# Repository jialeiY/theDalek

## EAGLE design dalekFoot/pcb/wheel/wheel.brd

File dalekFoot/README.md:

## For USART Only

## Control Request Packet
Offset | Name | Content | Width<br />(Bytes)
-:|:-|:-:|-:
0 | Packet Header | 0x55 | 1
1 | Motor Power # 1 | xx | 1
2 | Motor Power # 2 | xx | 1
3 | Motor Power # 3 | xx | 1
4 | Motor Power # 4 | xx | 1
5 | Melody Index | xx | 1
6 | LED | xx | 1
7 | CRC for payload only | xx | 1
8 | Packet Ending | 0xAA | 1

## Sampling Data Packet

Offset | Name | Content | Width<br />(Bytes)
-:|:-|:-:|-:
0 | Packet Header | 0x55 | 1
1 | Timestamp (Milliseconds) | xx | 4
5 | Time Offset (Micro Seconds) | xx | 4
9 | Motor Encoder #1 | xx | 2
11 | Motor Encoder #2 | xx | 2
13 | Motor Encoder #3 | xx | 2
15 | Motor Encoder #4 | xx | 2
17 | Fast ADC Value #1 ~ #14 | xx | 28
45 | Slow ADC Index | xx | 1
46 | Slow ADC Value | xx | 2
48 | UserInput | xx | 1
49 | CRC for payload only | xx  | 1
50 | Packet Ending | 0xAA | 1

# dalekFoot
## System Architecture

## MCU components connection diagram

## Neuro Software Architecture

## Protocol
### Working Scenario

### Startup Scenario

### Timeout Scenario

# stm32

## Interrupt NVIC

* Systick is the top piority timer

## Timer

* Systick is the top piority timer
* Systick should not block other event, It should be async and just make a notify

## SPI

* Max speed = 1/2 PCLK, SPI2 = 21MHz; SPI1 = 42MHz

## TODO

o DMA for SPI communication
o communication with SPI in slave mode
o communication with SPI and calculate the CPU usage

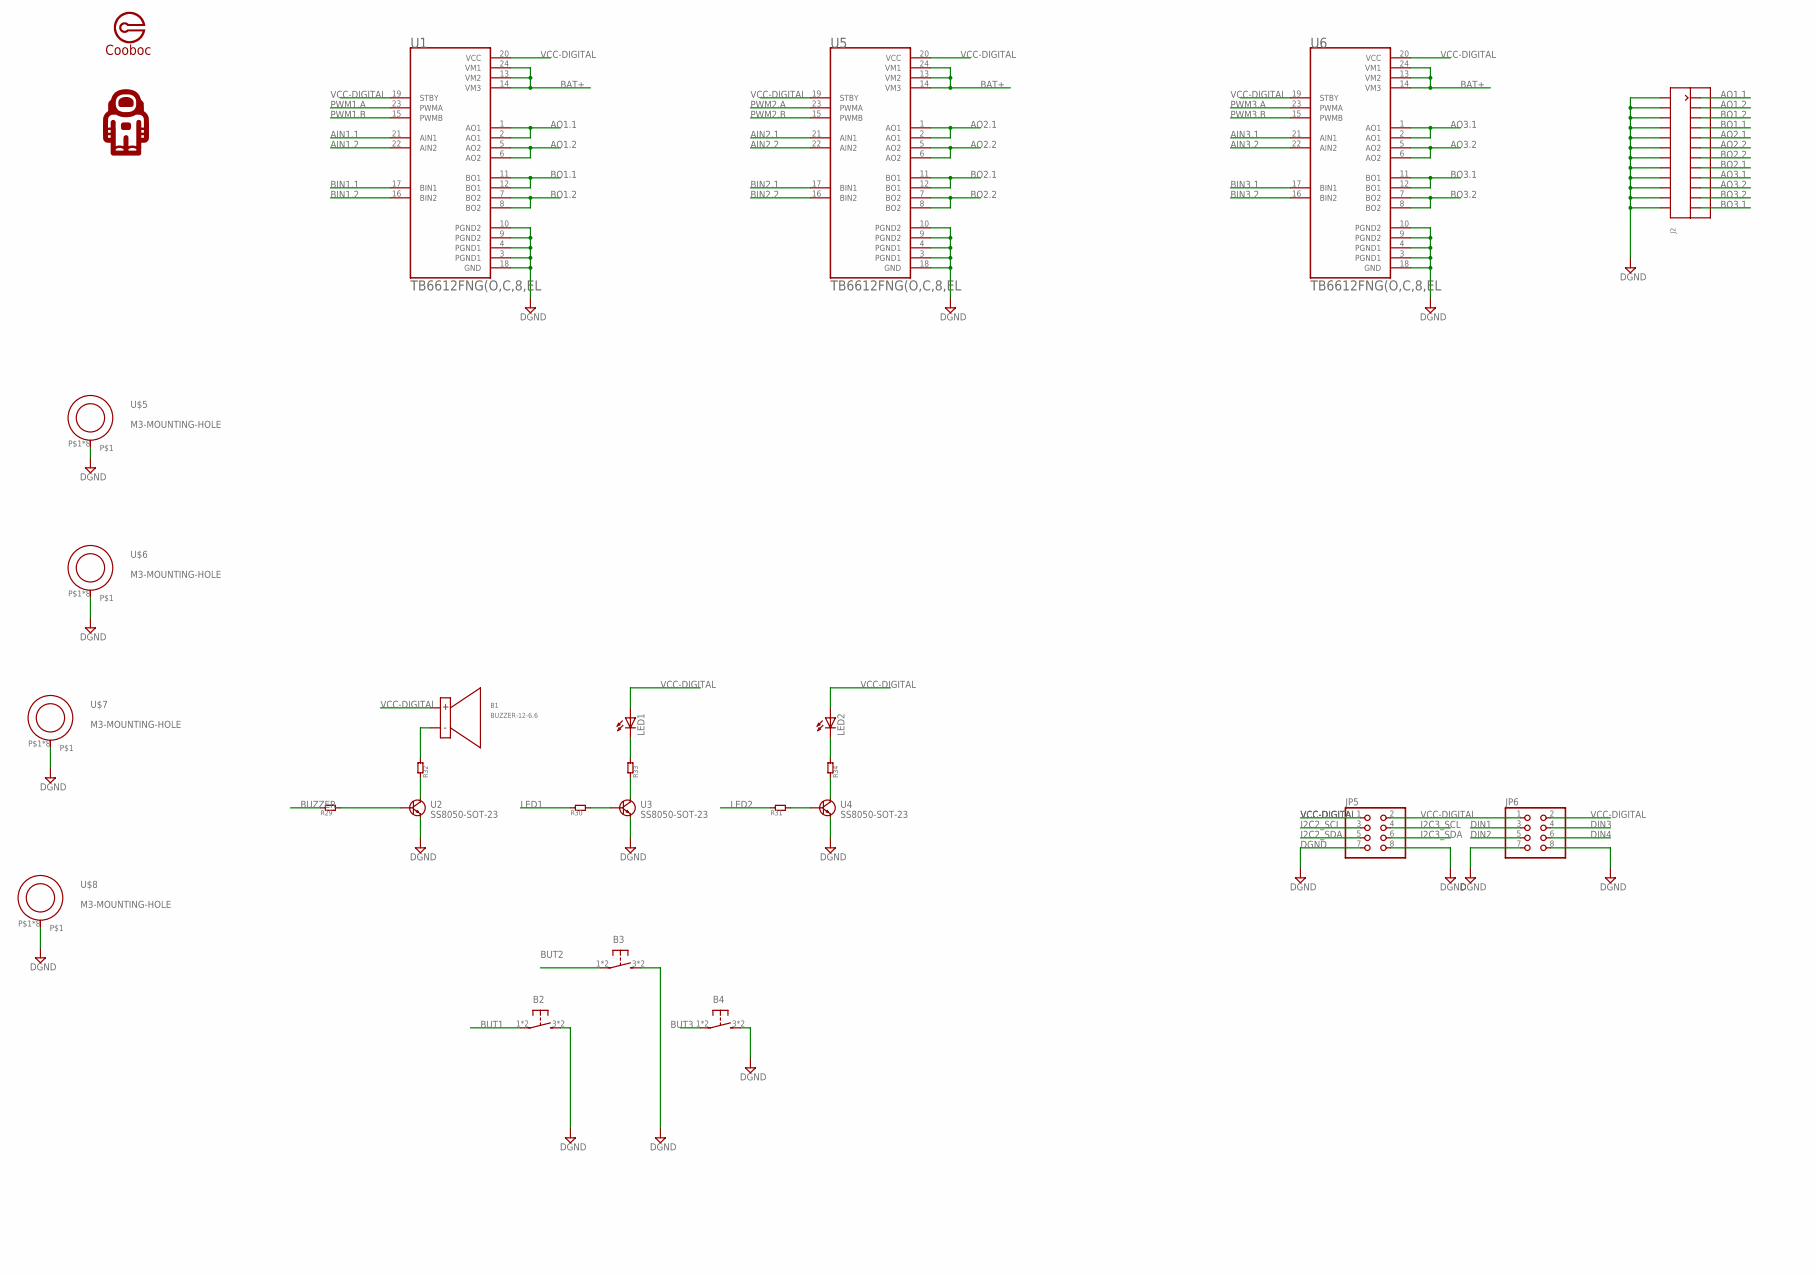
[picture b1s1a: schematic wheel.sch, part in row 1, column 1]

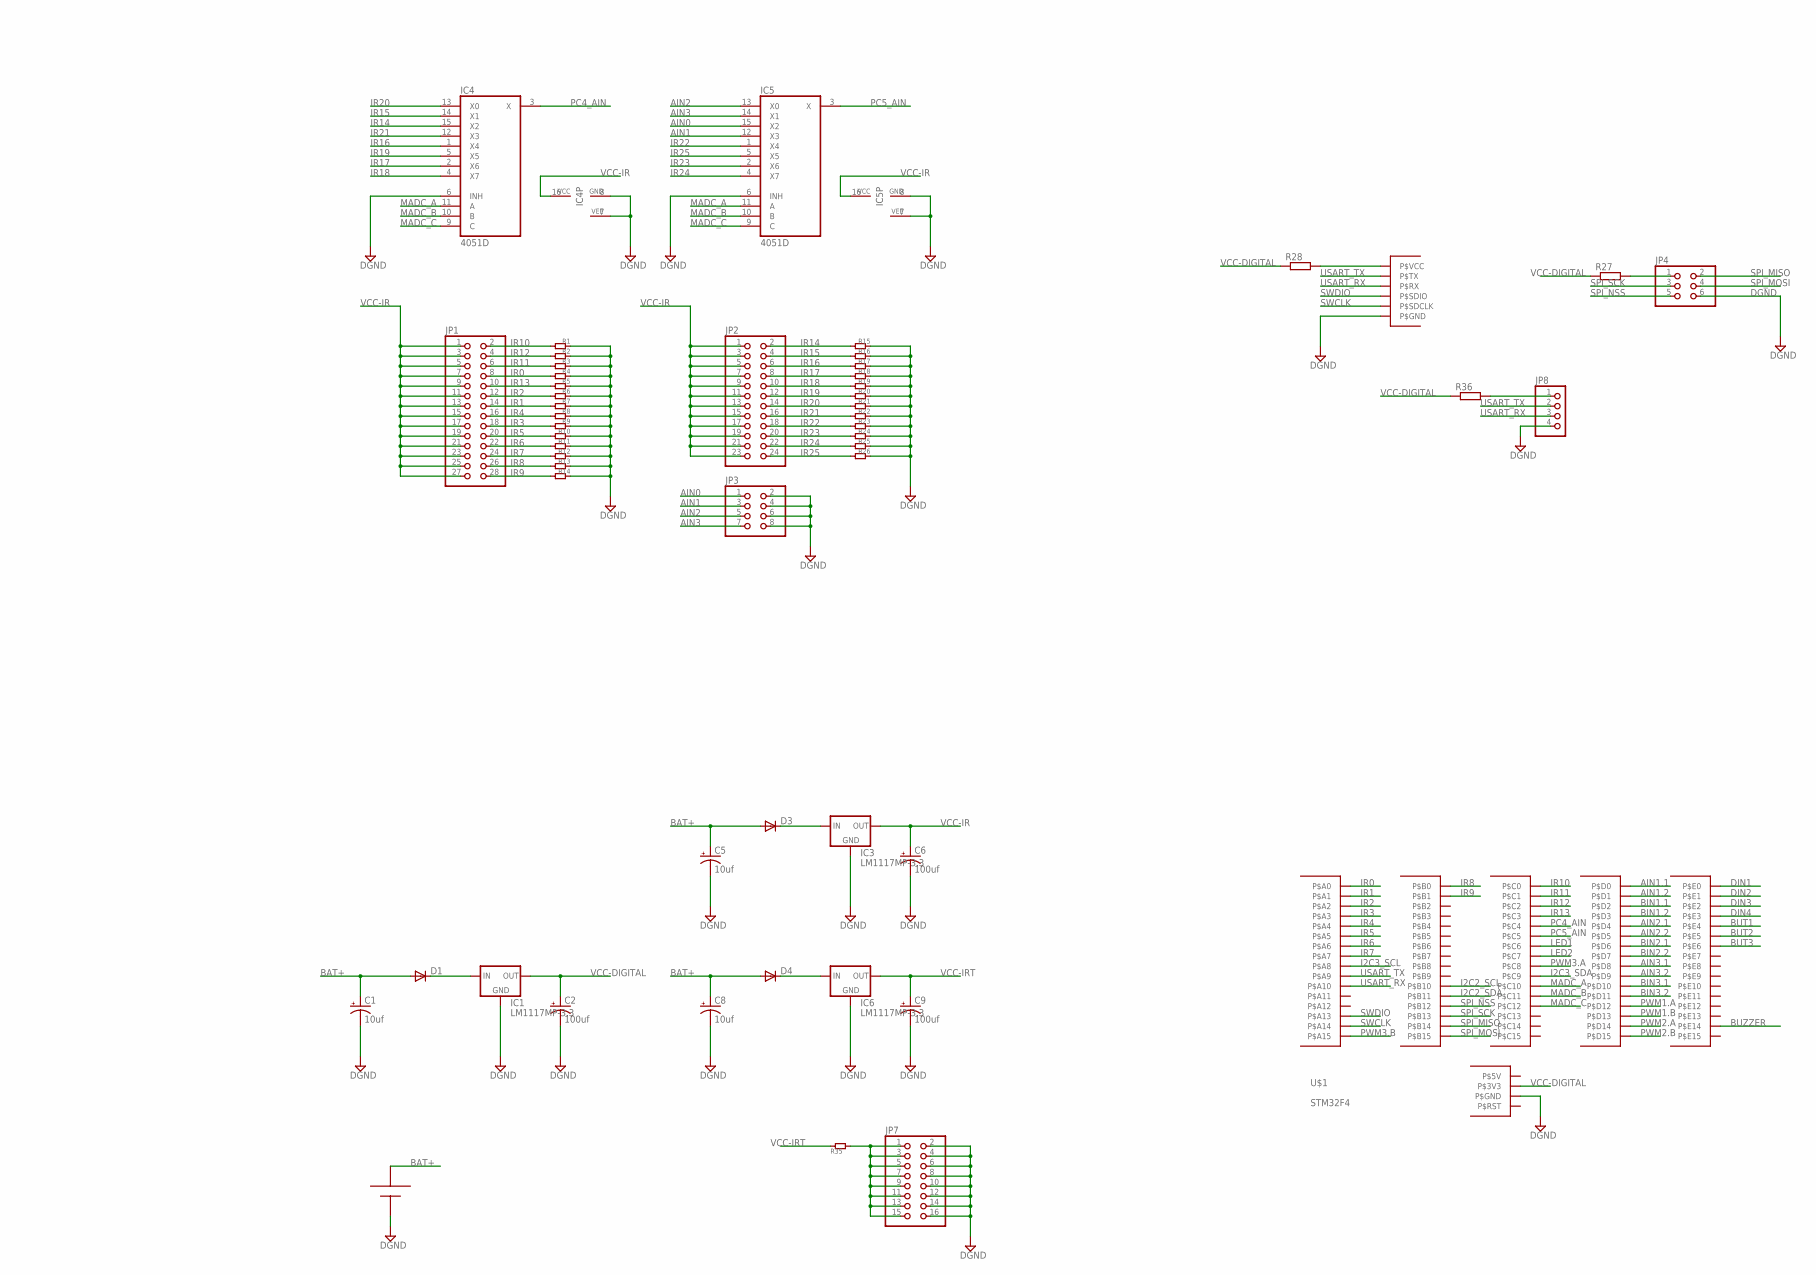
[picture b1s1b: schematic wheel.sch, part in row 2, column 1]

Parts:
B1: BUZZER-12-6.6
B2, B3, B4: DTSM-6-2PIN; DTSM-6
C1, C5, C8: 10uf; 153CLV-0505
C2, C6, C9: 100uf; 153CLV-0605
D1, D3, D4: DIODE-DO-214AC; DO-214AC
IC1, IC3, IC6: LM1117MP-3.3; SOT223
IC4, IC5: 4051D; SO16
J1: DEBUG-PORT
J2: KF250-2X12P
JP1: PINHD-2X14; 2X14
JP2: PINHD-2X12; 2X12
JP3, JP5, JP6: PINHD-2X4; 2X04
JP4: PINHD-2X3; 2X03
JP7: PINHD-2X8; 2X08
JP8: PINHD-1X4; 1X04
LED1, LED2: LEDCHIP-LED0805; CHIP-LED0805
R1, R2, R3, R4, R5, R6, R7, R8, R9, R10, R11, R12, R13, R14, R15, R16, R17, R18, R19, R20, R21, R22, R23, R24, R25, R26: R-0603; 0603
R27, R28, R36: R-EU_R0402; R0402
R29, R30, R31, R32, R33, R34, R35: R-0805; 0805
U1, U5, U6: TB6612FNG(O,C,8,EL; SOP65P760X160-24N
U2, U3, U4: SS8050-SOT-23; SOT-23
U$1: STM32F4
U$2: BATTERY-10A; BATTERY_10A
U$3: COOBOC-PLACE
U$4: ASTRONANT
U$5, U$6, U$7, U$8: M3-MOUNTING-HOLE

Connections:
AIN0: IC5.15 (X2), JP3.1
AIN1: IC5.12 (X3), JP3.3
AIN1.1: U1.21 (AIN1), U$1.P$22 (P$D0)
AIN1.2: U1.22 (AIN2), U$1.P$23 (P$D1)
AIN2: IC5.13 (X0), JP3.5
AIN2.1: U5.21 (AIN1), U$1.P$26 (P$D4)
AIN2.2: U5.22 (AIN2), U$1.P$27 (P$D5)
AIN3: IC5.14 (X1), JP3.7
AIN3.1: U6.21 (AIN1), U$1.P$49 (P$D8)
AIN3.2: U6.22 (AIN2), U$1.P$50 (P$D9)
AO1.1: J2.P$1, U1.1 (AO1), U1.2 (AO1)
AO1.2: J2.P$3, U1.5 (AO2), U1.6 (AO2)
AO2.1: J2.P$9, U5.1 (AO1), U5.2 (AO1)
AO2.2: J2.P$11, U5.5 (AO2), U5.6 (AO2)
AO3.1: J2.P$17, U6.1 (AO1), U6.2 (AO1)
AO3.2: J2.P$19, U6.5 (AO2), U6.6 (AO2)
BAT+: C1.+, C5.+, C8.+, D1.A, D3.A, D4.A, U1.13 (VM2), U1.14 (VM3), U1.24 (VM1), U5.13 (VM2), U5.14 (VM3), U5.24 (VM1), U6.13 (VM2), U6.14 (VM3), U6.24 (VM1), U$2.P$+ (P$POS)
BIN1.1: U1.17 (BIN1), U$1.P$24 (P$D2)
BIN1.2: U1.16 (BIN2), U$1.P$25 (P$D3)
BIN2.1: U5.17 (BIN1), U$1.P$28 (P$D6)
BIN2.2: U5.16 (BIN2), U$1.P$29 (P$D7)
BIN3.1: U6.17 (BIN1), U$1.P$51 (P$D10)
BIN3.2: U6.16 (BIN2), U$1.P$52 (P$D11)
BO1.1: J2.P$7, U1.11 (BO1), U1.12 (BO1)
BO1.2: J2.P$5, U1.7 (BO2), U1.8 (BO2)
BO2.1: J2.P$15, U5.11 (BO1), U5.12 (BO1)
BO2.2: J2.P$13, U5.7 (BO2), U5.8 (BO2)
BO3.1: J2.P$23, U6.11 (BO1), U6.12 (BO1)
BO3.2: J2.P$21, U6.7 (BO2), U6.8 (BO2)
BUT1: B2.1, B2.2 (1), U$1.P$61 (P$E4)
BUT2: B3.1, B3.2 (1), U$1.P$62 (P$E5)
BUT3: B4.1, B4.2 (1), U$1.P$63 (P$E6)
BUZZER: R29.P$1, U$1.P$41 (P$E14)
DGND: B2.3 (2), B2.4 (2), B3.3 (2), B3.4 (2), B4.3 (2), B4.4 (2), C1.-, C2.-, C5.-, C6.-, C8.-, C9.-, IC1.1 (GND), IC3.1 (GND), IC4.6 (INH), IC4.7 (VEE), IC4.8 (GND), IC5.6 (INH), IC5.7 (VEE), IC5.8 (GND), IC6.1 (GND), J1.P$7 (P$GND), J1.P$8 (P$GND), J2.P$2, J2.P$4, J2.P$6, J2.P$8, J2.P$10, J2.P$12, J2.P$14, J2.P$16, J2.P$18, J2.P$20, J2.P$22, J2.P$24, JP3.2, JP3.4, JP3.6, JP3.8, JP4.6, JP5.7, JP5.8, JP6.7, JP6.8, JP7.2, JP7.4, JP7.6, JP7.8, JP7.10, JP7.12, JP7.14, JP7.16, JP8.4, R1.P$1, R2.P$1, R3.P$1, R4.P$1, R5.P$1, R6.P$1, R7.P$1, R8.P$1, R9.P$1, R10.P$1, R11.P$1, R12.P$1, R13.P$1, R14.P$1, R15.P$1, R16.P$1, R17.P$1, R18.P$1, R19.P$1, R20.P$1, R21.P$1, R22.P$1, R23.P$1, R24.P$1, R25.P$1, R26.P$1, U1.3 (PGND1), U1.4 (PGND1), U1.9 (PGND2), U1.10 (PGND2), U1.18 (GND), U2.P$3 (P$E), U3.P$3 (P$E), U4.P$3 (P$E), U5.3 (PGND1), U5.4 (PGND1), U5.9 (PGND2), U5.10 (PGND2), U5.18 (GND), U6.3 (PGND1), U6.4 (PGND1), U6.9 (PGND2), U6.10 (PGND2), U6.18 (GND), U$1.P$1 (P$GND), U$1.P$2 (P$GND), U$1.P$3 (P$GND), U$1.P$91 (P$GND), U$1.P$92 (P$GND), U$2.P$- (P$NEG), U$5.P$1, U$5.P$2, U$5.P$3, U$5.P$4, U$5.P$5, U$5.P$6, U$5.P$7, U$5.P$8, U$6.P$1, U$6.P$2, U$6.P$3, U$6.P$4, U$6.P$5, U$6.P$6, U$6.P$7, U$6.P$8, U$7.P$1, U$7.P$2, U$7.P$3, U$7.P$4, U$7.P$5, U$7.P$6, U$7.P$7, U$7.P$8, U$8.P$1, U$8.P$2, U$8.P$3, U$8.P$4, U$8.P$5, U$8.P$6, U$8.P$7, U$8.P$8
DIN1: JP6.3, U$1.P$57 (P$E0)
DIN2: JP6.5, U$1.P$58 (P$E1)
DIN3: JP6.4, U$1.P$59 (P$E2)
DIN4: JP6.6, U$1.P$60 (P$E3)
I2C2_SCL: JP5.3, U$1.P$43 (P$B10)
I2C2_SDA: JP5.5, U$1.P$44 (P$B11)
I2C3_SCL: JP5.4, U$1.P$11 (P$A8)
I2C3_SDA: JP5.6, U$1.P$10 (P$C9)
IR0: JP1.8, R4.P$2, U$1.P$72 (P$A0)
IR1: JP1.14, R7.P$2, U$1.P$73 (P$A1)
IR2: JP1.12, R6.P$2, U$1.P$74 (P$A2)
IR3: JP1.18, R9.P$2, U$1.P$75 (P$A3)
IR4: JP1.16, R8.P$2, U$1.P$76 (P$A4)
IR5: JP1.20, R10.P$2, U$1.P$77 (P$A5)
IR6: JP1.22, R11.P$2, U$1.P$78 (P$A6)
IR7: JP1.24, R12.P$2, U$1.P$79 (P$A7)
IR8: JP1.26, R13.P$2, U$1.P$82 (P$B0)
IR9: JP1.28, R14.P$2, U$1.P$84 (P$B1)
IR10: JP1.2, R1.P$2, U$1.P$68 (P$C0)
IR11: JP1.6, R3.P$2, U$1.P$69 (P$C1)
IR12: JP1.4, R2.P$2, U$1.P$70 (P$C2)
IR13: JP1.10, R5.P$2, U$1.P$71 (P$C3)
IR14: IC4.15 (X2), JP2.2, R15.P$2
IR15: IC4.14 (X1), JP2.4, R16.P$2
IR16: IC4.1 (X4), JP2.6, R17.P$2
IR17: IC4.2 (X6), JP2.8, R18.P$2
IR18: IC4.4 (X7), JP2.10, R19.P$2
IR19: IC4.5 (X5), JP2.12, R20.P$2
IR20: IC4.13 (X0), JP2.14, R21.P$2
IR21: IC4.12 (X3), JP2.16, R22.P$2
IR22: IC5.1 (X4), JP2.18, R23.P$2
IR23: IC5.2 (X6), JP2.20, R24.P$2
IR24: IC5.4 (X7), JP2.22, R25.P$2
IR25: IC5.5 (X5), JP2.24, R26.P$2
LED1: R30.P$1, U$1.P$7 (P$C6)
LED2: R31.P$1, U$1.P$8 (P$C7)
MADC_A: IC4.11 (A), IC5.11 (A), U$1.P$19 (P$C10)
MADC_B: IC4.10 (B), IC5.10 (B), U$1.P$20 (P$C11)
MADC_C: IC4.9 (C), IC5.9 (C), U$1.P$21 (P$C12)
unnamed: D4.C, IC6.3 (IN)
unnamed: JP8.1, R36.2
unnamed: JP4.1, R27.2
unnamed: D1.C, IC1.3 (IN)
unnamed: JP7.1, JP7.3, JP7.5, JP7.7, JP7.9, JP7.11, JP7.13, JP7.15, R35.P$2
unnamed: J1.P$1 (P$VCC), J1.P$2 (P$VCC), R28.2
unnamed: R30.P$2, U3.P$1 (P$B)
unnamed: R31.P$2, U4.P$1 (P$B)
unnamed: R29.P$2, U2.P$1 (P$B)
unnamed: R32.P$1, U2.P$2 (P$C)
unnamed: R33.P$1, U3.P$2 (P$C)
unnamed: R34.P$1, U4.P$2 (P$C)
unnamed: B1.P$-, R32.P$2
unnamed: LED1.C, R33.P$2
unnamed: LED2.C, R34.P$2
unnamed: D3.C, IC3.3 (IN)
PC4_AIN: IC4.3 (X), U$1.P$80 (P$C4)
PC5_AIN: IC5.3 (X), U$1.P$81 (P$C5)
PWM1.A: U1.23 (PWMA), U$1.P$53 (P$D12)
PWM1.B: U1.15 (PWMB), U$1.P$54 (P$D13)
PWM2.A: U5.23 (PWMA), U$1.P$55 (P$D14)
PWM2.B: U5.15 (PWMB), U$1.P$56 (P$D15)
PWM3.A: U6.23 (PWMA), U$1.P$9 (P$C8)
PWM3.B: U6.15 (PWMB), U$1.P$18 (P$A15)
SPI_MISO: JP4.2, U$1.P$47 (P$B14)
SPI_MOSI: JP4.4, U$1.P$48 (P$B15)
SPI_NSS: JP4.5, U$1.P$45 (P$B12)
SPI_SCK: JP4.3, U$1.P$46 (P$B13)
SWCLK: J1.P$3 (P$SDCLK), U$1.P$17 (P$A14)
SWDIO: J1.P$5 (P$SDIO), U$1.P$16 (P$A13)
USART_RX: J1.P$4 (P$RX), JP8.3, U$1.P$13 (P$A10)
USART_TX: J1.P$6 (P$TX), JP8.2, U$1.P$12 (P$A9)
VCC-DIGITAL: B1.P$+, C2.+, IC1.2 (OUT), IC1.4 (OUT), JP5.1, JP5.2, JP6.1, JP6.2, LED1.A, LED2.A, R27.1, R28.1, R36.1, U1.19 (STBY), U1.20 (VCC), U5.19 (STBY), U5.20 (VCC), U6.19 (STBY), U6.20 (VCC), U$1.P$5 (P$3V3), U$1.P$6 (P$3V3), U$1.P$88 (P$3V3)
VCC-IR: C6.+, IC3.2 (OUT), IC3.4 (OUT), IC4.16 (VCC), IC5.16 (VCC), JP1.1, JP1.3, JP1.5, JP1.7, JP1.9, JP1.11, JP1.13, JP1.15, JP1.17, JP1.19, JP1.21, JP1.23, JP1.25, JP1.27, JP2.1, JP2.3, JP2.5, JP2.7, JP2.9, JP2.11, JP2.13, JP2.15, JP2.17, JP2.19, JP2.21, JP2.23
VCC-IRT: C9.+, IC6.2 (OUT), IC6.4 (OUT), R35.P$1

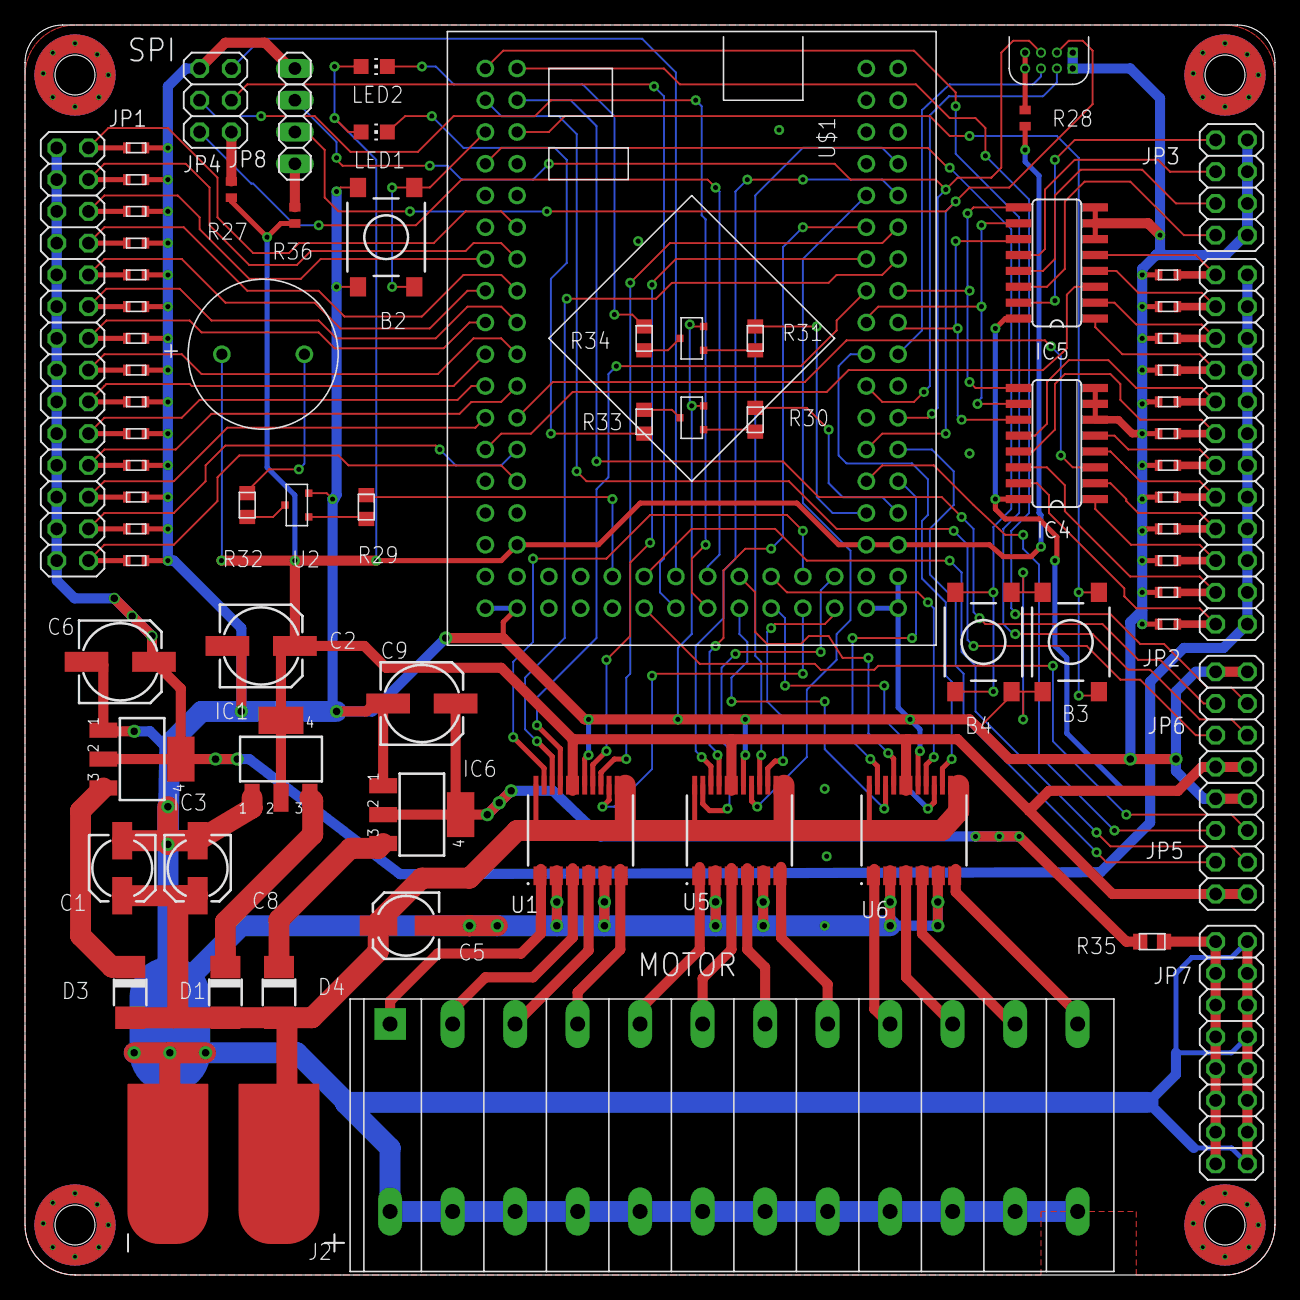
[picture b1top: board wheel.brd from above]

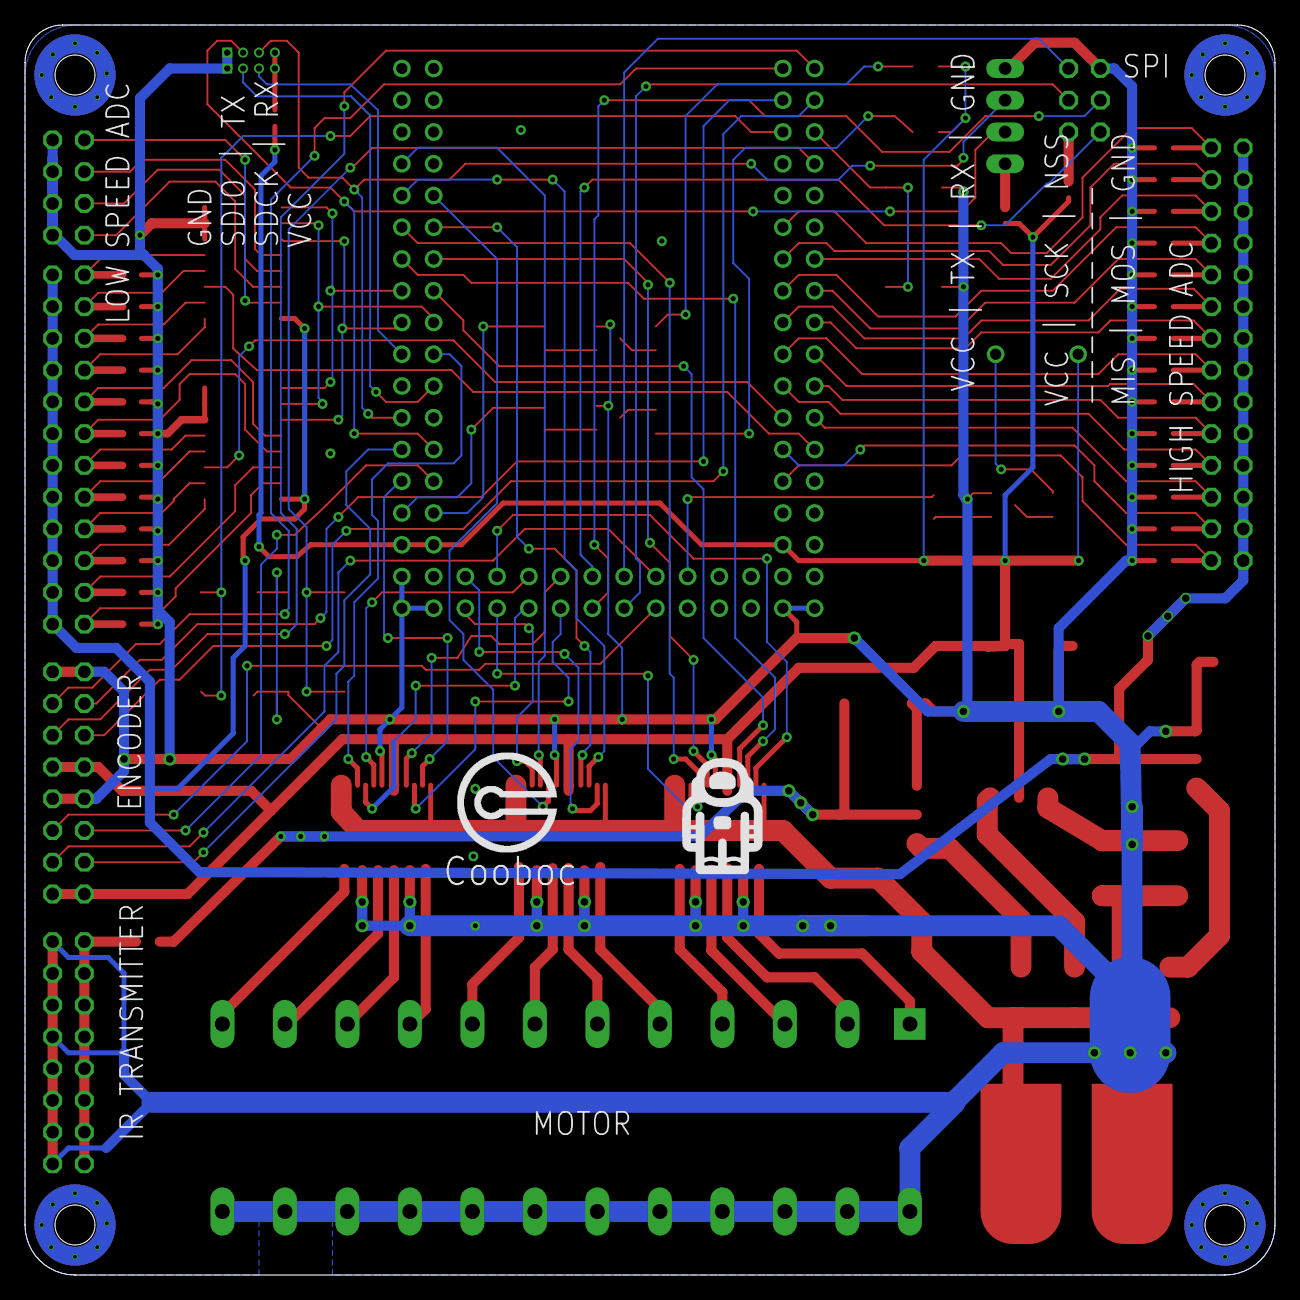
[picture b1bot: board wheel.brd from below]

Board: 2 copper layers, 100.0 x 100.0 mm, 80 parts (2 on the bottom side), 108 nets.

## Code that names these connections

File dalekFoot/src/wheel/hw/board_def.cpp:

#include "hw/board_def.h"
#include "ch.h"
#include "hal.h"





/***
 * 
 * Motor Connections
 * 
 *  ** Driver 1 ** 
 * AIN1 PD0
 * AIN2 PD1
 * BIN1 PD2
 * BIN2 PD3
 * PWMA PD12 (TIMER 4_1 AF(2))
 * PWMB PD13 (TIMER 4_2 AF(2))
 * 
 *  ** Driver 2 ** 
 * AIN1 PD4
 * AIN2 PD5
 * BIN1 PD6
 * BIN2 PD7
 * PWMA PD14 (TIMER 4_3 AF(2))
 * PWMB PD15 (TIMER 4_4 AF(2))
 * 
 *  ** Driver 3 ** 
 * AIN1 PD8
 * AIN2 PD9
 * BIN1 PD10
 * BIN2 PD11
 * PWMA PC8 (TIMER 3_3 AF(2))
 * PWMB PA15 (TIMER 2_1 AF(2))
 * 
 * 
 * 
 * ** LED **
 * led1 PC6 (Timer 3_1 AF(2), Timer 8_1 AF(3))
 * led2 PC7 (Timer 3_2 AF(2), Timer 8_2 AF(3))
 * Led3 PB9 (Timer 4_4 AF(2))
 * 
 * ** Buzzer **
 *  PE14 (Timer 1_4 AF(1))
 ***/

static PWMConfig pwm1Cfg {
	20000,
	100,                                  /* Initial PWM period 1S.         */
	NULL,                                     /* Period callback.               */
	{
	{PWM_OUTPUT_ACTIVE_HIGH, NULL},          		/* CH1 mode and callback.         */
	{PWM_OUTPUT_ACTIVE_HIGH, NULL},             /* CH2 mode and callback.         */
	{PWM_OUTPUT_ACTIVE_HIGH, NULL},             /* CH3 mode and callback.         */
	{PWM_OUTPUT_ACTIVE_HIGH, NULL}              /* CH4 mode and callback.         */
	},
	0,                                        /* Control Register 2.            */
	0                                         /* DMA/Interrupt Enable Register. */
};

static PWMConfig pwm3Cfg {
	5120000,
	256,                                  		/* Initial PWM period 1S.         */
	NULL,                                     /* Period callback.               */
	{
	{PWM_OUTPUT_ACTIVE_HIGH, NULL},          		/* CH1 mode and callback.         */
	{PWM_OUTPUT_ACTIVE_HIGH, NULL},             /* CH2 mode and callback.         */
	{PWM_OUTPUT_ACTIVE_HIGH, NULL},             /* CH3 mode and callback.         */
	{PWM_OUTPUT_ACTIVE_HIGH, NULL}              /* CH4 mode and callback.         */
	},
	0,                                        /* Control Register 2.            */
	0                                         /* DMA/Interrupt Enable Register. */
};

static PWMConfig pwm4Cfg {
	5120000,
	256,                                  /* Initial PWM period 1S.         */
	NULL,                                     /* Period callback.               */
	{
	{PWM_OUTPUT_ACTIVE_HIGH, NULL},          		/* CH1 mode and callback.         */
	{PWM_OUTPUT_ACTIVE_HIGH, NULL},             /* CH2 mode and callback.         */
	{PWM_OUTPUT_ACTIVE_HIGH, NULL},             /* CH3 mode and callback.         */
	{PWM_OUTPUT_ACTIVE_HIGH, NULL}              /* CH4 mode and callback.         */
	},
	0,                                        /* Control Register 2.            */
	0                                         /* DMA/Interrupt Enable Register. */
};




// BoardDef kBoardDef {
// 	&PWMD4,
// 	0,
// 	&pwm4Cfg,
// 	GPIOD,
// 	12
// };


BoardDef kBoardDef {
	// motor 1A
	&PWMD4,
	0,
	&pwm4Cfg,
	GPIOD,
	12,
	2,

	// motor 1B
	&PWMD4,
	1,
	&pwm4Cfg,
	GPIOD,
	13,
	2,

	// LED 1
	&PWMD3,
	0,
	&pwm3Cfg,
	GPIOC,
	6,
	2,
	
	// LED 2
	&PWMD3,
	1,
	&pwm3Cfg,
	GPIOC,
	7,
	2,
	
	// LED 3
	&PWMD4,
	3,
	&pwm4Cfg,
	GPIOB,
	9,
	2,

	// Buzzer
	&PWMD1,
	3,
	&pwm1Cfg,
	GPIOE,
	14,
	1
};

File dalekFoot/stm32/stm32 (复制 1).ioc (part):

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Mcu.Name=STM32F407V(E-G)Tx
Mcu.Package=LQFP100
Mcu.UserName=STM32F407VETx
PA0-WKUP.Signal=ADCx_IN0
PA1.Signal=ADCx_IN1
PA10.Mode=Asynchronous
PA10.Signal=USART1_RX
PA13.Mode=Serial_Wire
PA13.Signal=SYS_JTMS-SWDIO
PA14.Mode=Serial_Wire
PA14.Signal=SYS_JTCK-SWCLK
PA15.Signal=S_TIM2_CH1_ETR
PA2.Signal=ADCx_IN2
PA3.Signal=ADCx_IN3
PA4.Signal=ADCx_IN4
PA5.Signal=ADCx_IN5
PA6.Signal=ADCx_IN6
PA7.Signal=ADCx_IN7
PA8.Mode=I2C
PA8.Signal=I2C3_SCL
PA9.Mode=Asynchronous
PA9.Signal=USART1_TX
PB0.Signal=ADCx_IN8
PB1.Signal=ADCx_IN9
PB10.Mode=I2C
PB10.Signal=I2C2_SCL
PB11.Mode=I2C
PB11.Signal=I2C2_SDA
PB12.Mode=NSS_Signal_Hard_Input
PB12.Signal=SPI2_NSS
PB13.Mode=Full_Duplex_Slave
PB13.Signal=SPI2_SCK
PB14.Mode=Full_Duplex_Slave
PB14.Signal=SPI2_MISO
PB15.Mode=Full_Duplex_Slave
PB15.Signal=SPI2_MOSI
PC0.Signal=ADCx_IN10
PC1.Signal=ADCx_IN11
PC10.Signal=GPIO_Output
PC11.Signal=GPIO_Output
PC12.Signal=GPIO_Output
PC14-OSC32_IN.Mode=LSE-External-Oscillator
PC14-OSC32_IN.Signal=RCC_OSC32_IN
PC15-OSC32_OUT.Mode=LSE-External-Oscillator
PC15-OSC32_OUT.Signal=RCC_OSC32_OUT
PC2.Signal=ADCx_IN12
PC3.Signal=ADCx_IN13
PC4.Signal=ADCx_IN14
PC5.Signal=ADCx_IN15
PC6.Signal=GPIO_Output
PC7.Signal=GPIO_Output
PC8.Signal=S_TIM3_CH3
PC9.Mode=I2C
PC9.Signal=I2C3_SDA
PD0.Signal=GPIO_Output
PD1.Signal=GPIO_Output
PD10.Signal=GPIO_Output
PD11.Signal=GPIO_Output
PD12.Signal=S_TIM4_CH1
PD13.Signal=S_TIM4_CH2
PD14.Signal=S_TIM4_CH3
PD15.Signal=S_TIM4_CH4
PD2.Signal=GPIO_Output
PD3.Signal=GPIO_Output
PD4.Signal=GPIO_Output
PD5.Signal=GPIO_Output
PD6.Signal=GPIO_Output
PD7.Signal=GPIO_Output
PD8.Signal=GPIO_Output
PD9.Signal=GPIO_Output
PE0.Signal=GPIO_Input
PE1.Signal=GPIO_Input
PE14.Signal=S_TIM1_CH4
PE2.Signal=GPIO_Input
PE3.Signal=GPIO_Input
PE4.Signal=GPIO_Input
PE5.Signal=GPIO_Input
PE6.Signal=GPIO_Input
PH0-OSC_IN.Mode=HSE-External-Oscillator
PH0-OSC_IN.Signal=RCC_OSC_IN
PH1-OSC_OUT.Mode=HSE-External-Oscillator
PH1-OSC_OUT.Signal=RCC_OSC_OUT
RCC.HSE_VALUE=8000000
RCC.SYSCLKFreq_VALUE=168000000
RCC.SYSCLKSource=RCC_SYSCLKSOURCE_PLLCLK
board=custom

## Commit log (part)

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2021-04-09 add logo
2021-04-09 move logo position
2021-04-09 add cam file
2021-04-09 generate gerber files
2021-04-20 update submodule
2021-04-20 keep camera position in arduino
2021-04-22 move unused files into archive folder
2021-04-22 Add ChibiOS
2021-04-23 add move control to web
2021-04-23 can blink led
2021-04-23 can compile flash stm32f407
2021-04-25 adjust arduino motor pin
2021-04-26 can control motor using tb6612fng
2021-04-26 porting board configuration file
2021-04-26 move hardware related files into cfg folder
2021-04-26 can control motor speed
2021-04-26 refactor: move pin def out of tb6612
2021-04-27 can control led
2021-04-27 can control buzzer
2021-04-29 add motor datasheet
2021-04-30 bugfix: use allinc instead of using every inc
2021-04-30 can output using usart using printf
2021-04-30 change ChibiOS to tags/ver18.2.0
2021-04-30 make g++ framework
2021-04-30 refactor Makefile
2021-05-01 can toggle led using standard libary and C
2021-05-01 can compile with CPP
2021-05-01 move first try code to archive
2021-05-01 bugfix: fix typo in gitmodule
2021-05-01 move library
2021-05-01 move old code to archive
2021-05-02 enable systick
2021-05-03 pwm works
2021-05-03 can read encoder using exti
2021-05-04 can output using usart
2021-05-04 add serial files
2021-05-04 usart can write using ring buffer
2021-05-04 serial can support printf
2021-05-04 can read encoder speed
2021-05-05 Can read ADC2 using interrupt method
    Card: #59718479
2021-05-07 can read from slow and fast ADC
2021-05-07 bugfix: clearance too small on debug port
2021-05-08 jetson nano can playaudio
2021-05-08 Multiple bug fixed
    1. add mouting holes
    2. remove capacitor for buzzer
2021-05-08 optimize bottom route
2021-05-08 optimize route and cover pour
2021-05-09 add mcu soc communication protocol diagram
2021-05-09 add MCU SoC communication payload protocol
2021-05-09 add c++ source folder for SoC
2021-05-09 WIP: ready to read serial port
2021-05-10 add multi thread framework
2021-05-10 thread module can notify each other
2021-05-10 upgrade async framwork
2021-05-10 UNTEST: can decode mcu packet
2021-05-11 move timer function to standalone timer thread
2021-05-11 mcu can decode packet
2021-05-11 mcu can decode packet correctly
2021-05-12 bugfix: fix packet offset error
2021-05-12 trim input string from serial in arduino
2021-05-13 ready to read command
2021-05-18 bugfix: fix decode error and can read adc from mcu
2021-05-19 soc can send packet to mcu to contro motor speed
2021-05-21 Decrease pwm frequency to reduce noise on encoder signal line
2021-05-21 Add Neuro Architecture
2021-05-21 add pcb image
2021-05-21 WIP: Refactor Neuro framework
2021-05-22 add dalek brain architecture
2021-05-22 add dalek brain architecture png
2021-05-22 add dalek brain readme
2021-05-24 refactor: renme thread and ready to work
2021-05-24 double buffer done
2021-05-24 controller can read encoder
2021-05-25 fix typo
2021-05-25 Refactor action framework
2021-05-25 WIP: handling thread timeout situation
2021-05-26 WIP: refactor framework to loop + contorl thread
    Create the empty loop thread
2021-05-26 WIP: modify loop thread
2021-05-26 Add debug mode / Normal mode on board
2021-05-26 LoopThread now running in tick mode
2021-05-26 Change the time unit in LoopThread
2021-05-26 WIP: can decode packet from usart`
2021-05-26 remove unused files
2021-05-26 Refactor folder structure
2021-05-26 Refactor: move wheel sensor from hardware to sensor
2021-05-26 Try to modify baud rate
2021-05-27 fix pytorch scheduler and optimizer order
2021-05-27 ready to calculate wheel status
2021-05-27 WIP: calculate encoder start with 0
2021-05-28 wheel sensor can output wheel information
2021-05-28 Now wheel speed can be passed between action
2021-05-29 can control wheel speed using pid controller
2021-05-29 add qualifier to sensor
2021-06-02 add nanopi pinout
2021-06-03 Move thread related file into thread folder
2021-06-03 Refactor the brain, finish camera part
2021-06-03 Add argument parser
2021-06-04 Refactor: move logger to rtdp
2021-06-04 WIP: readyto write hardware to persistent file
2021-06-04 refactor speaker for brain
2021-06-04 remove pytorch-ssd as submodule
2021-06-05 UNTESTED: can write hardware data to persistent file
2021-06-05 Add todo
2021-06-05 Bugfix: fix copy memory error
2021-06-06 refactor partial nnLib for inference
2021-06-07 Enlarge ring buffer size for hardware output writer
2021-06-07 Can load hardware record file
2021-06-07 Refactor: move controller code from control_thread to standalone file
2021-06-07 Update output for debug
2021-06-07 integrate dalek recognition(too slow)
2021-06-07 WIP: Refactoring wheel sensor
2021-06-08 WIP: handle normal data
2021-06-08 Refactor wheel snesor, Now can handle unqualified data
2021-06-08 remove unused code
2021-06-08 Bugfix: fix speed calculation error
2021-06-08 Can handle encoder overflow
2021-06-08 WIP: debug why power jumping
2021-06-09 Show max fail count
2021-06-13 WIP: refactor object recognition part
2021-06-15 fix error of recognition
2021-06-20 init flask server
2021-06-20 connect vision output to flask
2021-08-26 refactor motor control. (haodadeyu haodadexiaoqiang TT)
2021-08-29 brain hacker for movement
2021-08-30 add back brain hacker for camera movement
2021-09-01 initiate object tracking
2021-09-03 [WIP] centroid object tracking
2021-09-03 intgrate object tracking
2024-04-04 Add some test codes
2024-04-05 add timer test code
2024-04-05 add vscode configuration
2024-04-06 can control gpio using timer in kernel
2024-06-09 add stm32 files
2024-06-09 update ignore files
2024-06-09 add vscode configuration file
2024-06-11 Add spi tester
2024-06-11 add motor driver datasheet
2024-06-11 add romp
2024-06-13 remove stm32 folder
2024-06-13 can compile main
2024-06-14 can send uart in sychonroinized way
2024-06-14 can send via uart by interrupt mode
2024-06-14 Can send uart in DMA mode
2024-06-14 refactor third party library
2024-06-14 WIP: refactor
2024-06-16 can SPI communication
2024-06-18 refactor SPI
2024-06-18 refactor serial
2024-06-20 Remove pub sub
2024-06-20 can generate pwm
2024-06-22 Motors done
2024-07-03 Add 3d parts
2024-07-03 update requirements
2024-07-03 Reduce the height of encoder holder
2024-07-03 remove conflict with tail screw
2024-07-03 increase diameter of gear shaft
2024-07-03 move fix hole into the body
2024-07-03 space for encoder singal wires
2024-07-06 timer 5 works
2024-07-06 update encoder documentation
2024-07-06 I2C can capture timer interrupt
2024-07-06 can generate 300khz clock signal
2024-07-07 can read ack
2024-07-07 Can read data from encoder
2024-07-10 can control speed using PID
2024-07-11 optimize the i2c speed
2024-07-13 can control motor speed in dynamic
2024-07-13 can control speed via SPI
2024-07-18 ready to read four motor
2024-07-19 add todo list
2024-07-20 Can print data after one cycle using intent framework
2024-07-21 Increase systick interrupt priority
2024-07-21 decrease the priority of main cycle
2024-07-21 WIP: support multiple I2C reading simultaneously
2024-07-21 Can read 2 I2C device simultaneously
2024-07-21 Can read 4 I2C simultaneously
2024-07-21 can print all wheel speed
2024-07-21 refactor parameter to static value
2024-07-21 Can control all motor speed
2024-07-21 Update todo
2024-07-22 refactor move basic data def to common folder
2024-07-23 add time and duration
2024-07-23 change to metric unit
2024-07-24 update PID parameters
2024-07-24 test low speed performance
2024-07-27 increase uart baud rate
2024-07-27 Intent framework
2024-07-28 hahah can write debug data to mcap
2024-07-28 remove reference code
2024-07-28 add output of foxglove extensions to gitignore
2024-07-28 can draw lines on foxglove
2024-07-28 update reamde
2024-07-29 add data module
2024-07-31 Add PositioningIntent
2024-08-01 rename positioning to odometry
2024-08-01 add mock odometry
2024-08-02 WIP: odometry
2024-08-02 Update robot model
2024-08-02 can show robot position on foxglove
2024-08-02 add simulation screenshot image
2024-08-03 Add routetopic converter
2024-08-03 Can write route to mcap
2024-08-03 can show route in foxglove can show route in foxglove can show route in foxglove
2024-08-03 calculate init state of ego on the route
2024-08-03 yolo
2024-08-04 Change Vector2D to PolarVector
2024-08-04 add position to protobuf
2024-08-04 take position2d back
2024-08-04 write EgoStateTopic to mcap
2024-08-04 Ego and world coordinate transform
2024-08-04 update foxglove layout
2024-08-04 can show ego velocity on foxglove
2024-08-04 increase arrow head length of acceleration
2024-08-05 WIP: lateral planning
2024-08-06 bugfix: fix vec to polarvec bug
2024-08-09 Bugfix: update last velocity after calcluation
2024-08-09 Restrict the maximum acceleration to avoid force suddently changed
2024-08-10 WIP: introduce PID module
2024-08-10 optimize the grid on 3d panel
2024-08-10 WIP: Analysis core dumps
2024-08-10 Bugfix: ego velocity to frenet velocity
2024-08-11 Add TrajectoryIntent
2024-08-11 WIP: trajectoryIntent
2024-08-13 WIP: ready to draw beizer curve
2024-08-15 WIP: refactor RouteIntent
2024-08-16 fixbug to debug rouet intent
2024-08-16 add missing library
2024-08-16 Update Route visualization
2024-08-16 change name from uniform to constant
2024-08-17 WIP trajectory
2024-08-17 can make a simple trajectory
2024-08-18 make adaptor smoother on bezier curve
2024-08-18 extend route for testing
2024-08-18 Quadratic bezier finished
2024-08-18 GagaIntent skeleton
2024-08-18 WIP: simulator
2024-08-19 add 3d model file
2024-08-19 add vehicle request topic
2024-08-19 Can calculate the wheel speed
2024-08-19 WIP: refactor debug data writer
2024-08-20 WIP: refacotr debug writer`
2024-08-21 refactor DebugWriterIntent done
2024-08-21 WIP: odometry and sim
2024-08-21 simulator done
2024-08-23 Can get the calculation duration of intents
2024-08-27 move trajectory code to standalone file
2024-08-28 save polar vector of each trajectory segment
2024-08-28 Calculate longitudinal - curvature profile
2024-08-30 bugfix: correct the curvature profile
2024-08-31 Refactor: move profile calculating to standalone file
2024-08-31 longitudinal profile based on curvature
2024-09-01 can calculate frenet
2024-09-01 bugfix: frenet converter
2024-09-01 ready to planning longitudinal
2024-09-04 Increase maximum acceleration value
2024-09-05 write vehicle response to mcap
2024-09-06 bugfix: fix the pose calculation error
2024-09-07 longitudinal planning done
2024-09-07 can follow trajectory
2024-09-11 ready to write communication protocol between gaga and haha
2024-09-16 ready to communication from pc to gaga
2024-09-17 Gaga can follow the spi command
2024-09-18 change back to encoder controlling
2024-09-18 can control wheel using spi
2024-09-21 add CRC from haha to gaga
    and fine tunning the spimaster timing
2024-09-22 gaga can send spi packet with crc
2024-09-26 can genreate ghpacket in haha
2024-09-27 WIP: update spi protocol, resolve compiling errors
2024-09-27 udpate SPI protocol, SIL done
2024-09-27 Could stop at end of the route
2024-09-27 reduce maximum speed to test the hardware
2024-09-28 ready to test hardware
2024-09-28 update spi protocol
2024-09-28 Add empty shadowVehicle and rename egoState to egoMotionState
2024-09-28 Clean unused data type: VelicheReponse
2024-09-28 can compile now
2024-10-01 update formater rules
2024-10-01 Refactor: make trajectory to reference path
2024-10-01 update namespace
2024-10-01 Refactor: trajectoryIntent to referencePathIntent
2024-10-01 ready to refactor behavior intent
2024-10-05 refactor behavior intent and topic
2024-10-09 WIP: refactoring the route topic, ready to refactor referencepath
2024-10-10 Fix route bug and update route foxglove plugin
2024-10-10 udpate ref
2024-10-11 remove empty folder
2024-10-12 add comments
2024-10-13 add position struct
2024-10-15 WIP: refactor and implement the frenet
2024-10-26 refactor: make topic POD
2024-10-26 align communcation packate to 4
2024-10-28 Route codec for static polyline
2024-10-30 add test framework
2024-10-31 Frenet calculation
2024-11-12 genreate control points for reference path
2024-11-13 can generate coverage report
2024-11-21 add test for vertex property
2024-11-23 Add tests and fix bugs
2024-11-23 vertex propert tests done

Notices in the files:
parts and their libraries:
lm1117: (c) 2014 Samuel Lourenço
